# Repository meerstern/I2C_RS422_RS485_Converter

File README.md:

# I2C-RS422/485変換基板 

I2C-RS422/485 Converter with Grove Connector

## 概要 
  * マイコンのI2CポートをRS422/RS485通信ポートに変換するアダプタです  
  * 本アダプタでI2Cから半二重RS422/RS485の送信、受信処理をすることができます  
  * マイコンからI2Cデバイスとして制御し、送受信の他、RS422/RS485のボーレート設定等をすることができます
  * I2C/UARTプロトコルブリッジ[SC16IS750][1]とRS422/RS485変換IC [ST3485EIDT][2]を搭載しています
  * I2CはGrove互換コネクタとなっており、3.3V/5V電源に対応しています
  * RS422/RS485ポートは2.54mmピッチネジ止め端子を搭載しています(VDD,RS422/485+,RS422/485-,GND)  
  * I2C/UARTプロトコルブリッジSC16IS750は64bytesのバッファを内蔵しています
  * 7.3728MHzの水晶発振子を搭載しており、マイコンのメインクロックから独立してRS422/RS485のボーレート設定ができます 
  * デフォルトI2Cアドレスは8bit:0x9A(7bit:0x4D)です  
  * 半二重RS422/RS485通信のため、送信時はRTSをHigh、送信時以外はRTSをLowにして使用してください    
  * 終端抵抗RX2は未実装です  必要に応じて終端抵抗をRX2もしくは端子台に接続してください  
  * 基板サイズ33mm x24mm、固定穴M3x2 幅18mm  

## 注意 
  * Arduino Uno以外の場合はサンプルコード内SC16IS750.cppの29行目付近のWire定義を必要に応じて変更してください  

## 販売サイト
  * [スイッチサイエンス][3]

[1]: https://www.nxp.com/products/peripherals-and-logic/signal-chain/bridges/single-uart-with-i2c-bus-spi-interface-64-bytes-of-transmit-and-receive-fifos-irda-sir-built-in-support:SC16IS740_750_760 "*1"
[2]: https://www.st.com/ja/interfaces-and-transceivers/st3485ei.html "*2"
[3]: https://www.switch-science.com/products/7395
MIT Lisense

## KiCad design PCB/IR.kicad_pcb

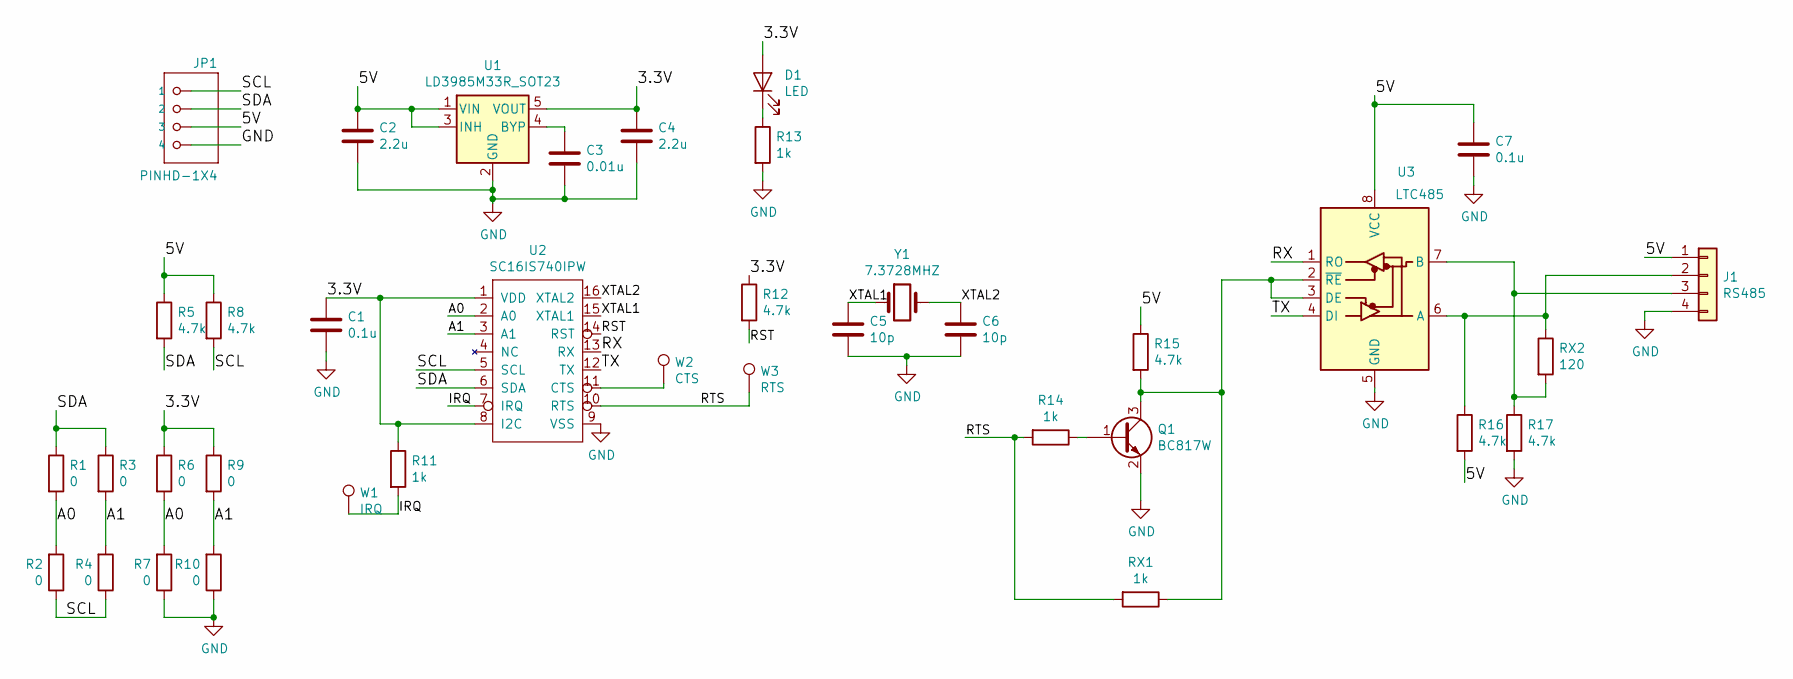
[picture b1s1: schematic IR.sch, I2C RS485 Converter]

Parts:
C1, C7: 0.1u; C_0603_1608Metric
C2, C4: 2.2u; C_0805_2012Metric
C3: 0.01u; C_0603_1608Metric
C5, C6: 10p; C_0603_1608Metric
D1: LED; D_0603_1608Metric
J1: RS485; PinHeader_1x04_P2.54mm_Vertical
JP1: PINHD-1X4; GROVE
Q1: BC817W; SOT-323_SC-70
R1, R2, R3, R4, R6, R7, R9, R10: 0; R_0603_1608Metric
R5, R8, R12, R15, R16, R17: 4.7k; R_0603_1608Metric
R11, R13, R14: 1k; R_0603_1608Metric
RX1: 1k; R_0603_1608Metric
RX2: 120; R_0603_1608Metric
U1: LD3985M33R_SOT23; SOT-23-5
U2: SC16IS740IPW; TSSOP-16_4.4x5mm_Pitch0.65mm
U3: LTC485; SO-8_3.9x4.9mm_P1.27mm
W1: IRQ; TestPoint_THTPad_D1.0mm_Drill0.5mm
W2: CTS; TestPoint_THTPad_D1.0mm_Drill0.5mm
W3: RTS; TestPoint_THTPad_D1.0mm_Drill0.5mm
Y1: 7.3728MHZ; Crystal_SMD_HC49-SD

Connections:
/3.3V: C1.1, C4.1, D1.2 (A), R6.1, R9.1, R11.1, R12.1, U1.5 (VOUT), U2.1 (VDD), U2.8 (I2C)
/5V: C2.1, C7.1, J1.1, JP1.3, R5.1, R8.1, R15.1, R16.2, U1.1 (VIN), U1.3 (INH), U3.8 (VCC)
/A0: R1.2, R2.2, R6.2, R7.2, U2.2 (A0)
/A1: R3.2, R4.2, R9.2, R10.2, U2.3 (A1)
/IRQ: R11.2, U2.7 (IRQ), W1.1; also elsewhere on the board
/RST: R12.2, U2.14 (RST)
/RTS: R14.2, RX1.2, U2.10 (RTS), W3.1; also elsewhere on the board
/RX: U2.13 (RX), U3.1 (RO)
/SCL: JP1.1, R2.1, R4.1, R8.2, U2.5 (SCL)
/SDA: JP1.2, R1.1, R3.1, R5.2, U2.6 (SDA)
/TX: U2.12 (TX), U3.4 (DI)
/XTAL1: C5.1, U2.15 (XTAL1), Y1.1
/XTAL2: C6.1, U2.16 (XTAL2), Y1.2
GND: C1.2, C2.2, C3.2, C4.2, C5.2, C6.2, C7.2, J1.4, JP1.4, Q1.2 (E), R7.1, R10.1, R13.2, R17.2, U1.2 (GND), U2.9 (VSS), U3.5 (GND)
unnamed: C3.1, U1.4 (BYP)
unnamed: D1.1 (K), R13.1
unnamed: J1.2, R16.1, RX2.1, U3.6 (A)
unnamed: J1.3, R17.1, RX2.2, U3.7 (B)
unnamed: Q1.1 (B), R14.1
unnamed: Q1.3 (C), R15.2, RX1.1, U3.2 (~RE), U3.3 (DE)
unnamed 20: U2.11 (CTS), W2.1; also elsewhere on the board

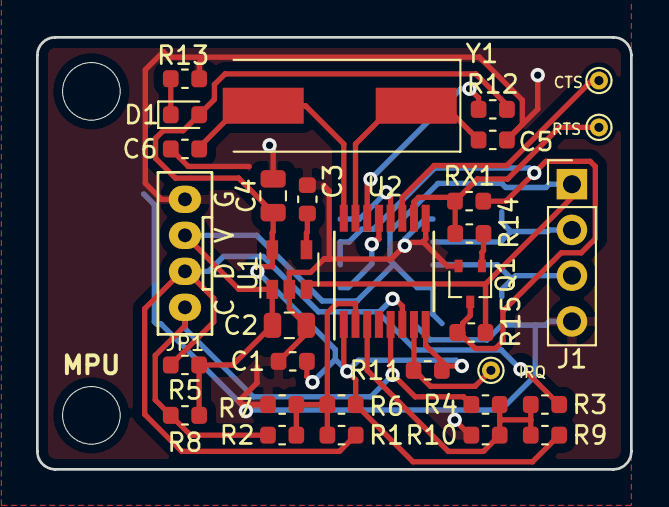
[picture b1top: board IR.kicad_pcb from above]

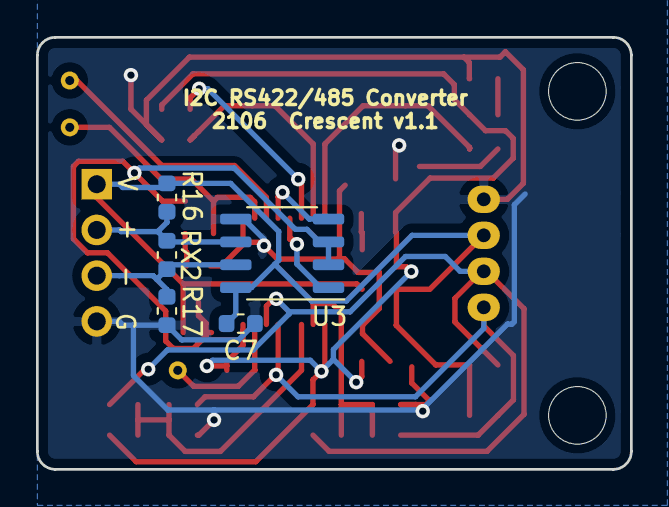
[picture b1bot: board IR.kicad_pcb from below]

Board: 2 copper layers, 33.0 x 24.0 mm, 39 parts (5 on the bottom side), 21 nets.

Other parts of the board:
CTS: CTS; TestPoint_THTPad_D1.0mm_Drill0.5mm
IRQ: IRQ; TestPoint_THTPad_D1.0mm_Drill0.5mm
REF1, REF3: MountingHole_3.2mm_M3
RTS: RTS; TestPoint_THTPad_D1.0mm_Drill0.5mm

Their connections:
/IRQ: IRQ.1; also elsewhere on the board
/RTS: RTS.1; also elsewhere on the board
unnamed 20: CTS.1; also elsewhere on the board

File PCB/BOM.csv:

Elecrow PN,Parts,Value,Package,QTY,Digikey/Mouser/Manufacturer Part,Remark/ Link
,JP1,PINHD-1X4,GROVE,1,713-110990037,
C14663,"C1,C7",0.1u,C_0603_1608Metric,2,,
C15850,"C2,C4",10u,C_0805_2012Metric,2,,
C57112,C3,0.01u,C_0603_1608Metric,1,,
C1644,"C5,C6",10p,C_0603_1608Metric,2,,
4040806A,D1,LED,D_0603_1608Metric,1,,
C25804,"R7,R10",10k,R_0603_1608Metric,2,,
C23162,"R5,R8,R12,R15,R16,R17",4.7k,R_0603_1608Metric,6,,
C21190,"R11,R13,R14,RX1",1k,R_0603_1608Metric,4,,
,U1,LD3985M33R_SOT23,SOT-23-5,1,511-LD3985M33R,
,Y1,7.3728MHZ,Crystal_SMD_HC49-SD,1,815-ABLS-7.3728-B2,
,U2,SC16IS740IPW,TSSOP-16_4.4x5mm_Pitch0.65mm,1,771-SC16IS0IPW128,
,J1,RS485,PinHeader_1x04_P2.54mm_Vertical,1,571-282834-4,
,Q1,BC817W,SOT-323_SC-70,1,771-BC817W115 ,
,U3,LTC485,SO-8_3.9x4.9mm_P1.27mm,1,511-ST3485EIDT ,

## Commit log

2021-06-30 Add PCB files
2021-07-06 Add README
2021-07-31 Add Sample Code
